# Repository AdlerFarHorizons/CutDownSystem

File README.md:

CutDownSystem
=============

Summary
-------
This is an arduino-based system for separating a high-altitude balloon from its payload under
pre-determined conditions.

Documentation
------------
The documentation available for this system is included in the /docs directory.

Software
--------
In order to run this system, two Arduino boards are required, assembled according to the SCHEMATIC
file. They are pre-programmed; to modify this system, a computer running Arduino IDE is required.
To program the Arduinos, upload new code as specified through the Arduino IDE to the CutDownBase.
The CutDownBase will wirelessly transfer pertinent code to the CutDownRemote.

Licensing
--------
Please see the file named LICENSE.

Contacts
--------

Lou Nigra
Adler Planetarium - Far Horizons Lab

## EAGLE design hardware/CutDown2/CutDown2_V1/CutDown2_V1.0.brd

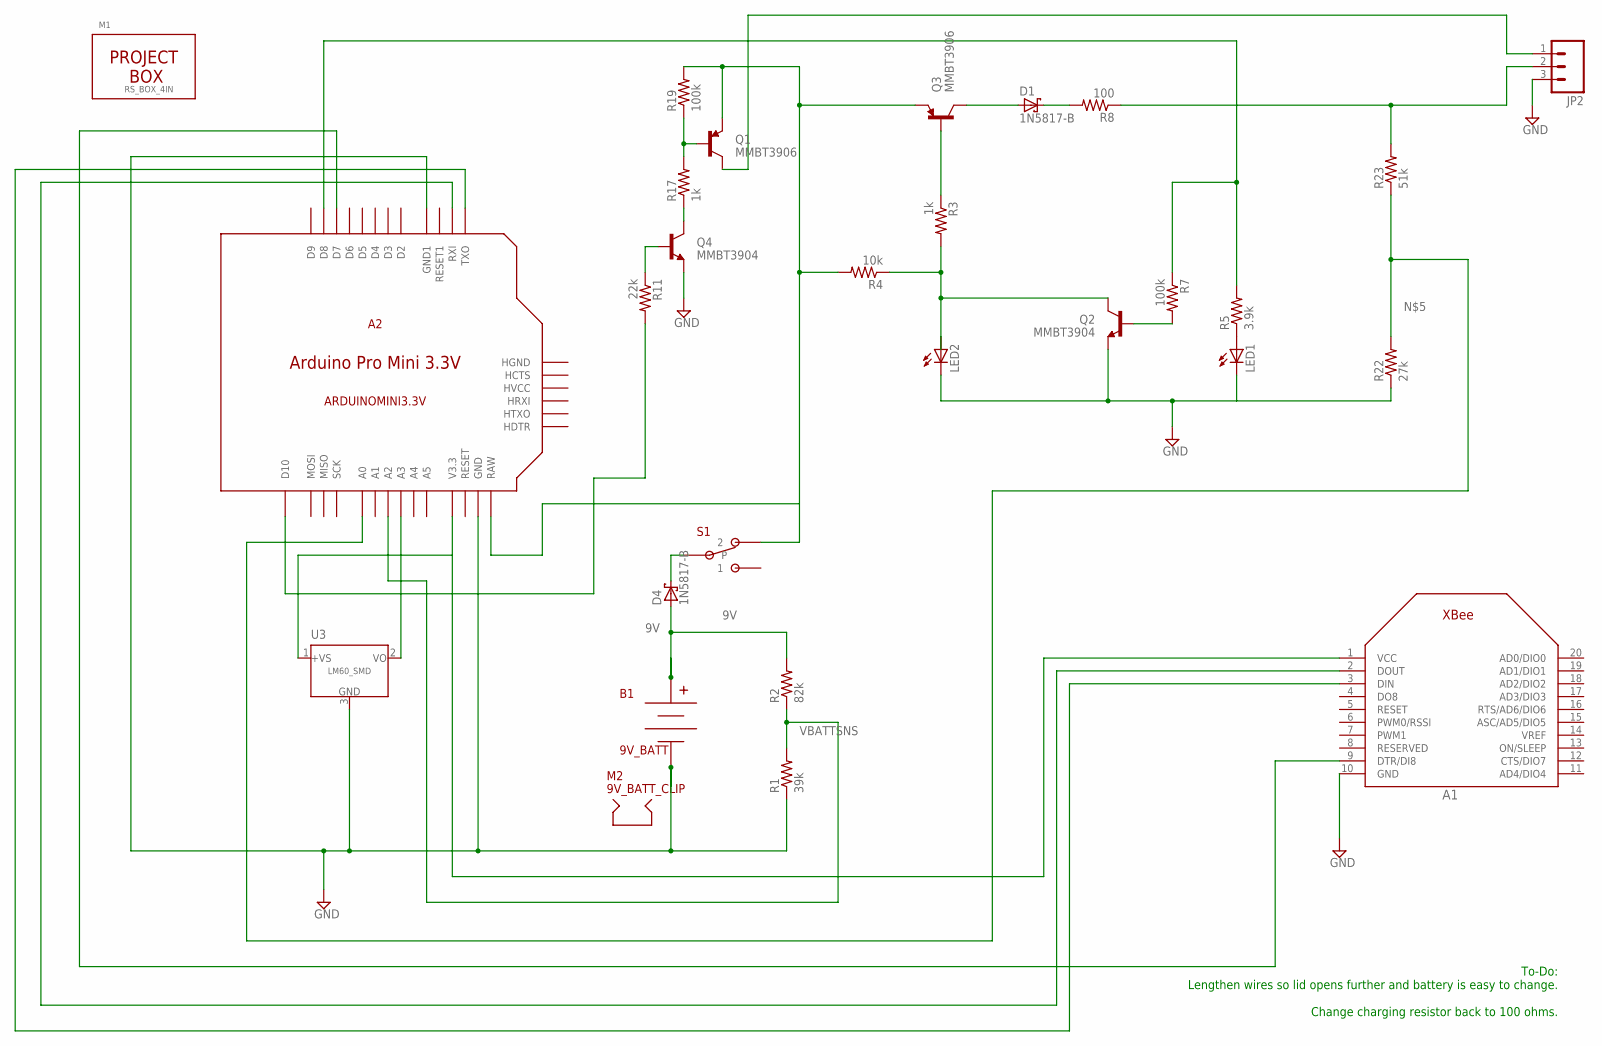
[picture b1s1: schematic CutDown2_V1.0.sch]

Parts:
A1: XBEE
A2: ARDUINOMINI3.3V
B1: 9V_BATT; KEYSTONE_593_594
D1, D4: 1N5817-B; DO41-7.6
JP2: M03POLAR_LOCK; MOLEX-1X3_LOCK
LED1, LED2: LED_ELD260; LED_LD260
M1: RS_BOX_4IN; RS_BOX_OUTLINE_4IN
M2: 9V_BATT_CLIP; KEYSTONE_9V_CLIP_H
Q1, Q3: MMBT3906; SOT23
Q2, Q4: MMBT3904; SOT23
R1: 39k; R0805
R2: 82k; R0805
R3, R17: 1k; R0805
R4: 10k; R0805
R5: 3.9k; R0805
R7, R19: 100k; R0805
R8: 100; R0805
R11: 22k; R0805
R22: 27k; R0805
R23: 51k; R0805
S1: APEM_SPDT_25000NH
U3: LM60_SMD; SOT23-3

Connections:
9V: B1.P$1 (V+), B1.P$2 (V+), B1.P$3 (V+), D4.A, R2.2
GND: A1.10 (GND), A2.P$9 (GND1), A2.P$20 (GND), B1.P$4 (V-), B1.P$5 (V-), B1.P$6 (V-), JP2.3, LED1.K (C), LED2.K (C), Q2.2 (E), Q4.2 (E), R1.1, R22.1, U3.3 (GND)
unnamed: Q3.1 (B), R3.1
unnamed: D1.A, Q3.3 (C)
unnamed: A2.P$2 (D8), R5.2, R7.1
unnamed: LED1.A, R5.1
unnamed: A2.P$26 (A0), R22.2, R23.1
unnamed: D1.C, R8.2
unnamed: LED2.A, Q2.3 (C), R3.2, R4.1
unnamed: A1.2 (DOUT), A2.P$11 (RXI)
unnamed: A2.P$23 (A3), U3.2 (VO)
unnamed: A1.3 (DIN), A2.P$12 (TXO)
unnamed: D4.C, S1.P$3
unnamed: Q2.1 (B), R7.2
unnamed: Q4.3 (C), R17.1
unnamed: Q1.1 (B), R17.2, R19.1
unnamed: JP2.1, Q1.3 (C)
unnamed: A2.P$30 (D10), R11.2
unnamed: Q4.1 (B), R11.1
unnamed: JP2.2, R8.1, R23.2
unnamed: A2.P$19 (RAW), Q1.2 (E), Q3.2 (E), R4.2, R19.2, S1.P$2 (2)
VBATTSNS: A2.P$24 (A2), R1.2, R2.1
VCC: A1.1 (VCC), A2.P$22 (V3.3), U3.1 (+VS)
VCSNS: A1.9 (DTR/DI8), A2.P$3 (D7)

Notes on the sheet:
To-Do: Lengthen wires so lid opens further and battery is easy to change. Change charging resistor back to 100 ohms.

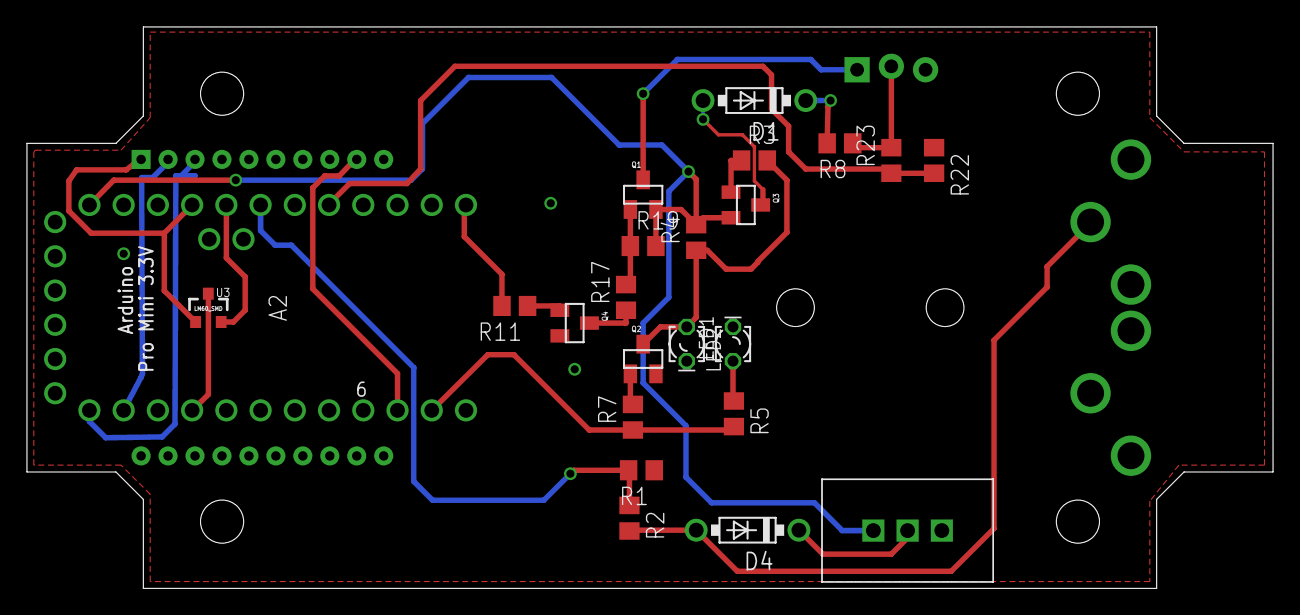
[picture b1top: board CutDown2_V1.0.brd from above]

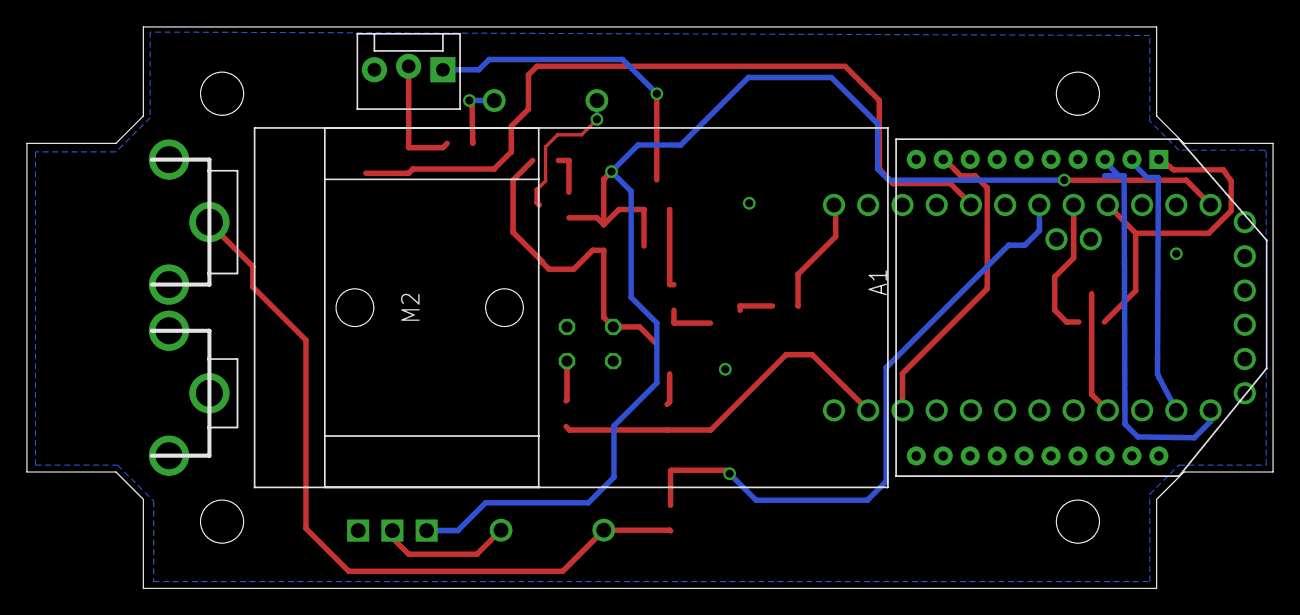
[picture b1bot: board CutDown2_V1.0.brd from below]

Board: 2 copper layers, 92.5 x 41.7 mm, 28 parts (4 on the bottom side), 24 nets.

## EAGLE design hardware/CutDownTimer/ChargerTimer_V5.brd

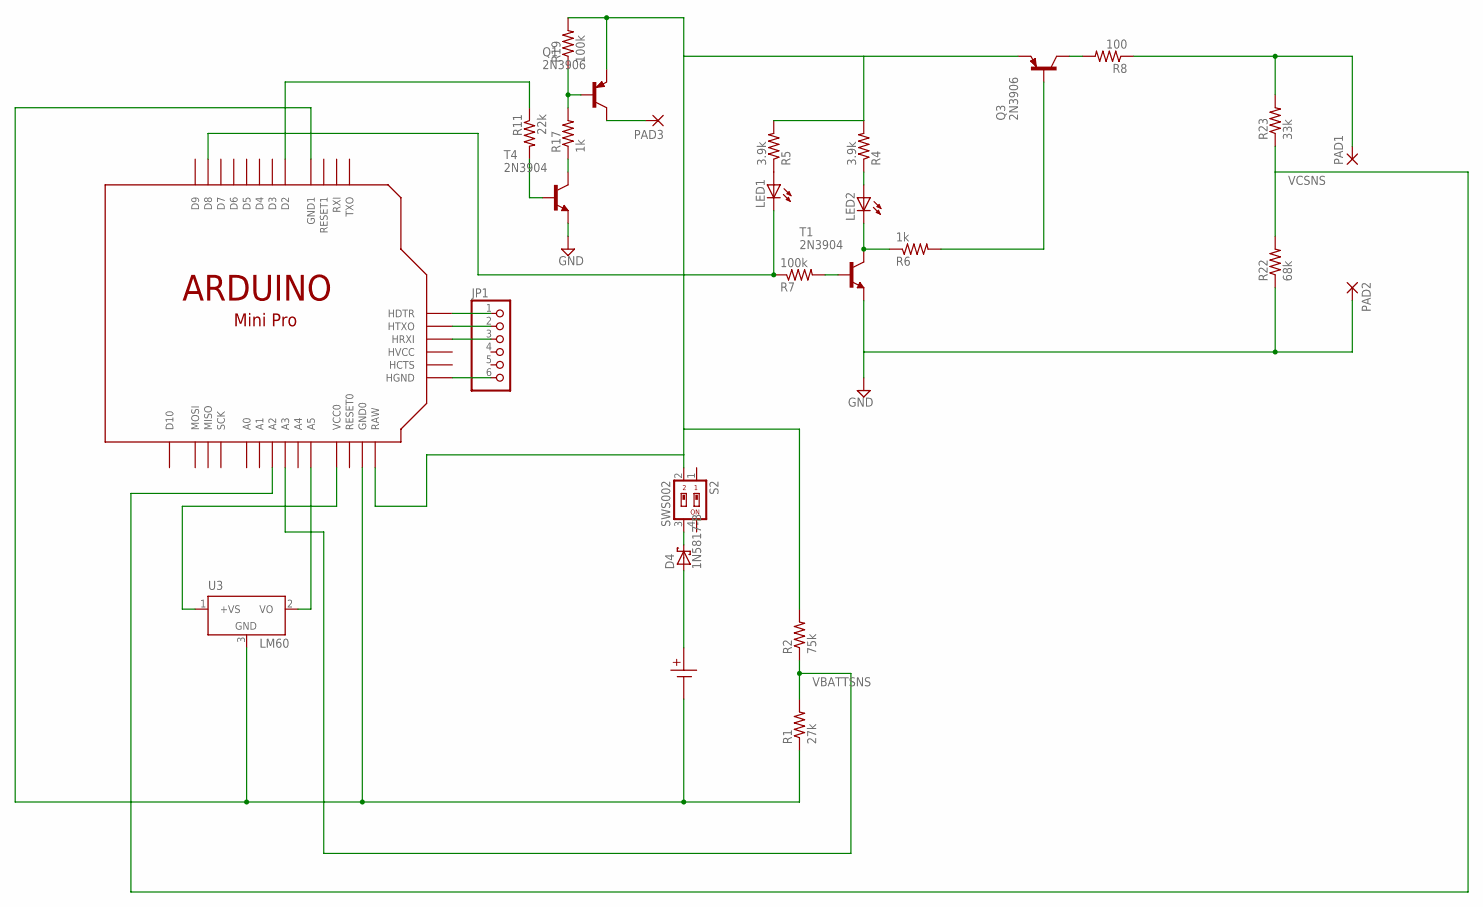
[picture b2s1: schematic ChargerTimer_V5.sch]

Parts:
D4: 1N5817-B; DO41-7.6
JP1: PINHD-1X6; 1X06
LED1, LED2: LED_ELD260; LED_LD260
PAD1, PAD2, PAD3: 2,15/1,0
Q1, Q3: 2N3906; TO92
R1: 27k; 0207/7
R2: 75k; 0207/7
R4, R5: 3.9k; 0207/7
R6, R17: 1k; 0207/7
R7, R19: 100k; 0207/7
R8: 100; 0207/7
R11: 22k; 0207/7
R22: 68k; 0207/7
R23: 33k; 0207/7
S2: SWS002; SMS-002
T1, T4: 2N3904; TO92
U3: LM60; TO92
U$1: BH1000G
U$4: ARDUINOMINI

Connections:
GND: T1.3 (E), T4.3 (E)
unnamed: Q3.1 (C), R8.2
unnamed: LED1.K (C), R7.1, U$4.P$2 (D8)
unnamed: LED1.A, R5.1
unnamed: LED2.A, R4.1
unnamed: LED2.K (C), R6.1, T1.1 (C)
unnamed: Q3.2 (B), R6.2
unnamed: D4.C, S2.3
unnamed: PAD2.1, R22.1
unnamed: R11.1, U$4.P$8 (D2)
unnamed: Q1.3 (E), Q3.3 (E), R2.2, R4.2, R5.2, R19.2, S2.2, U$4.P$19 (RAW)
unnamed: R7.2, T1.2 (B)
unnamed: R17.1, T4.1 (C)
unnamed: Q1.2 (B), R17.2, R19.1
unnamed: PAD3.1, Q1.1 (C)
unnamed: U3.2 (VO), U$4.P$35 (A5)
unnamed: JP1.1, U$4.P$13 (HDTR)
unnamed: U3.1 (+VS), U$4.P$22 (VCC0)
unnamed: R11.2, T4.2 (B)
unnamed: JP1.2, U$4.P$14 (HTXO)
unnamed: R1.1, U3.3 (GND), U$1.NEG$2 (P2), U$4.P$9 (GND1), U$4.P$20 (GND0)
unnamed: D4.A, U$1.POS$1 (P1)
unnamed: JP1.3, U$4.P$15 (HRXI)
unnamed: JP1.6, U$4.P$18 (HGND)
unnamed: PAD1.1, R8.1, R23.2
VBATTSNS: R1.2, R2.1, U$4.P$23 (A3)
VCSNS: R22.2, R23.1, U$4.P$24 (A2)

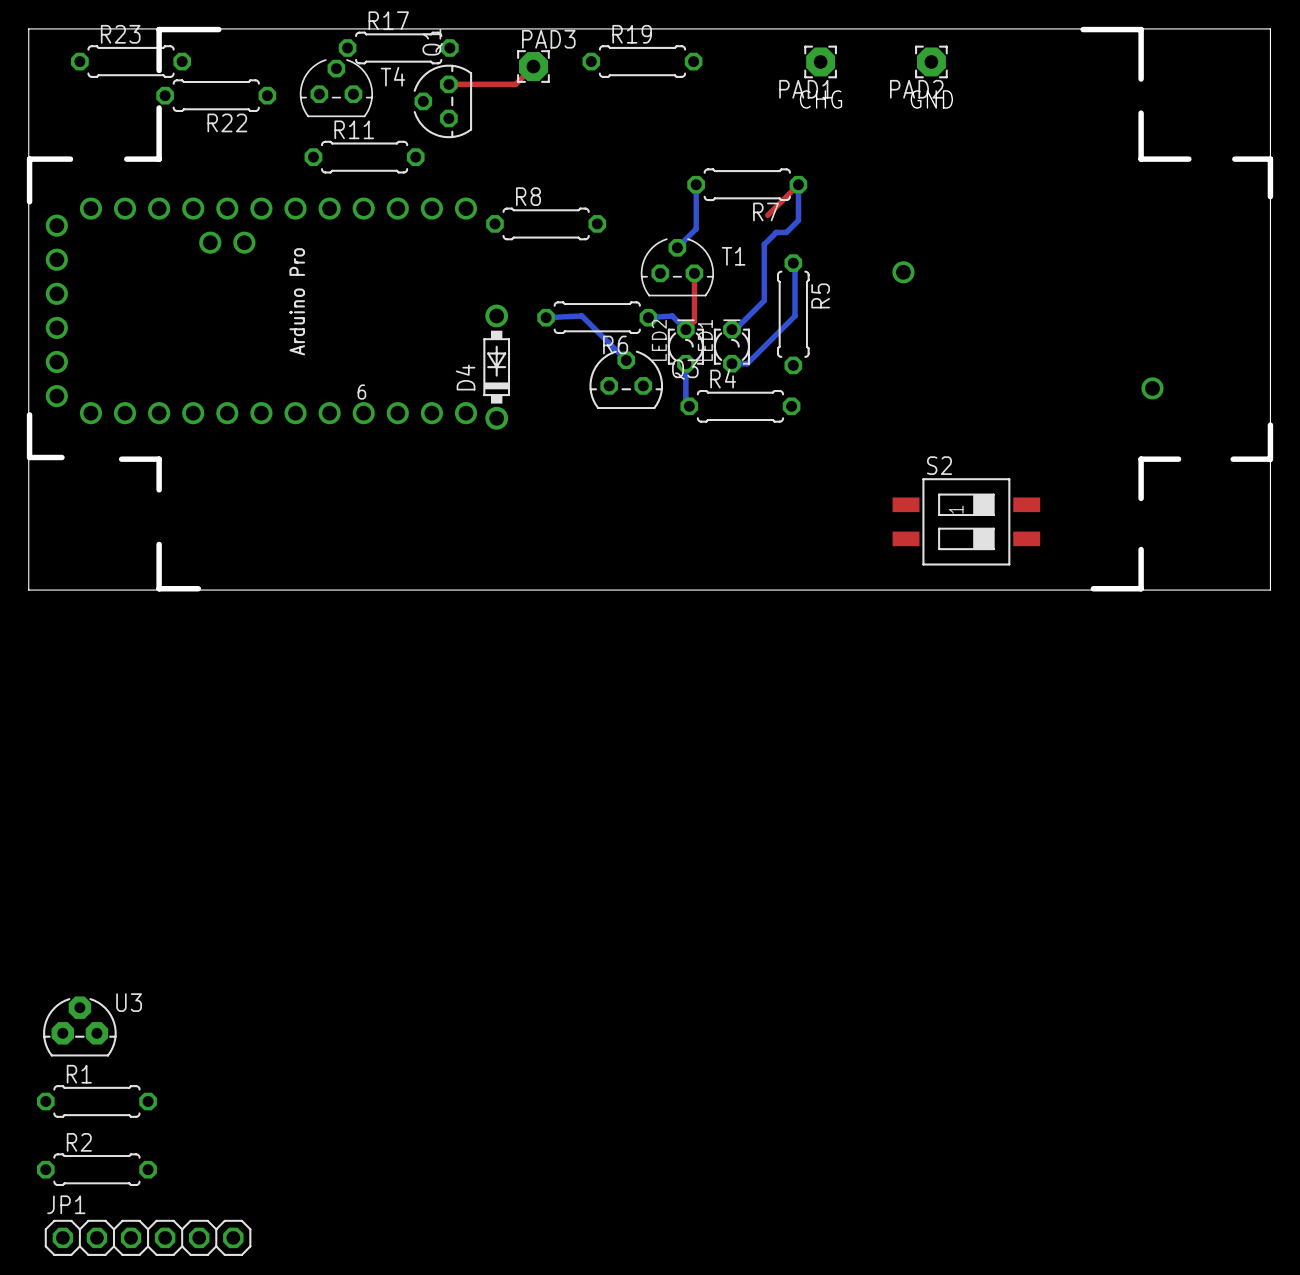
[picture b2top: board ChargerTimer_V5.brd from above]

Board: 2 copper layers, 92.5 x 41.8 mm, 27 parts (1 on the bottom side), 27 nets.

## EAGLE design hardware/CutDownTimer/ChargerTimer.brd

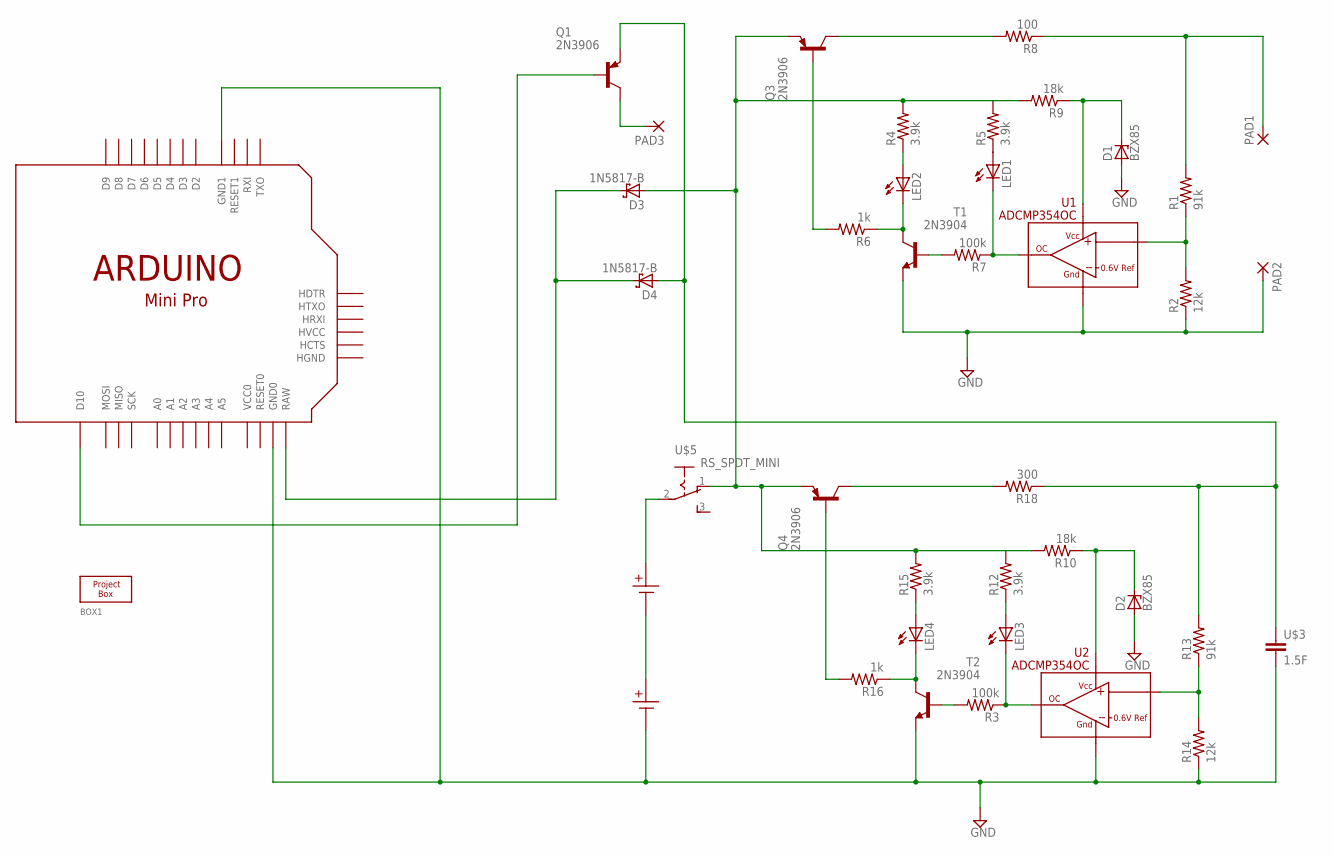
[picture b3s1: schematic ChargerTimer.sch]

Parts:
BOX1: RS_BOX_4IN; RS_BOX_OUTLINE_4IN
D1, D2: BZX85; DO41Z10
D3, D4: 1N5817-B; DO41-7.6
LED1, LED2, LED3, LED4: LED_ELD260; LED_LD260
PAD1, PAD2, PAD3: 2,15/1,0
Q1, Q3, Q4: 2N3906; TO92
R1, R13: 91k; 0207/7
R2, R14: 12k; 0207/7
R3, R7: 100k; 0207/7
R4, R5, R12, R15: 3.9k; 0207/7
R6, R16: 1k; 0207/7
R8: 100; 0207/7
R9, R10: 18k; 0207/7
R18: 300; 0207/7
T1, T2: 2N3904; TO92
U1, U2: ADCMP354OC; ADCMP35X
U$1, U$2: BH1000G
U$3: 1.5F; SUPERCAP1.0/0.85H
U$4: ARDUINOMINI
U$5: RS_SPDT_MINI

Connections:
GND: D1.A, D2.A, PAD2.1, R2.1, R14.1, T1.3 (E), T2.3 (E), U1.P2 (GND), U2.P2 (GND), U$2.NEG$2 (P2), U$3.P$2 (2), U$4.P$9 (GND1), U$4.P$20 (GND0)
unnamed: R1.1, R2.2, U1.P1 (IN)
unnamed: Q3.1 (C), R8.2
unnamed: LED1.K (C), R7.1, U1.P3 (OUT)
unnamed: LED1.A, R5.1
unnamed: LED2.A, R4.1
unnamed: LED2.K (C), R6.1, T1.1 (C)
unnamed: Q3.2 (B), R6.2
unnamed: PAD1.1, R1.2, R8.1
unnamed: R3.2, T2.2 (B)
unnamed: D4.A, Q1.3 (E), R13.2, R18.1, U$3.P$1 (1)
unnamed: U$1.POS$1 (P1), U$5.2
unnamed: U$1.NEG$2 (P2), U$2.POS$1 (P1)
unnamed: R7.2, T1.2 (B)
unnamed: D1.C, R9.1, U1.P4 (VCC)
unnamed: D2.C, R10.1, U2.P4 (VCC)
unnamed: R13.1, R14.2, U2.P1 (IN)
unnamed: LED3.K (C), R3.1, U2.P3 (OUT)
unnamed: LED3.A, R12.1
unnamed: LED4.A, R15.1
unnamed: LED4.K (C), R16.1, T2.1 (C)
unnamed: Q4.2 (B), R16.2
unnamed: Q4.1 (C), R18.2
unnamed: D3.A, Q3.3 (E), Q4.3 (E), R4.2, R5.2, R9.2, R10.2, R12.2, R15.2, U$5.1 (O)
unnamed: PAD3.1, Q1.1 (C)
unnamed: D3.C, D4.C, U$4.P$19 (RAW)
unnamed: Q1.2 (B), U$4.P$30 (D10)

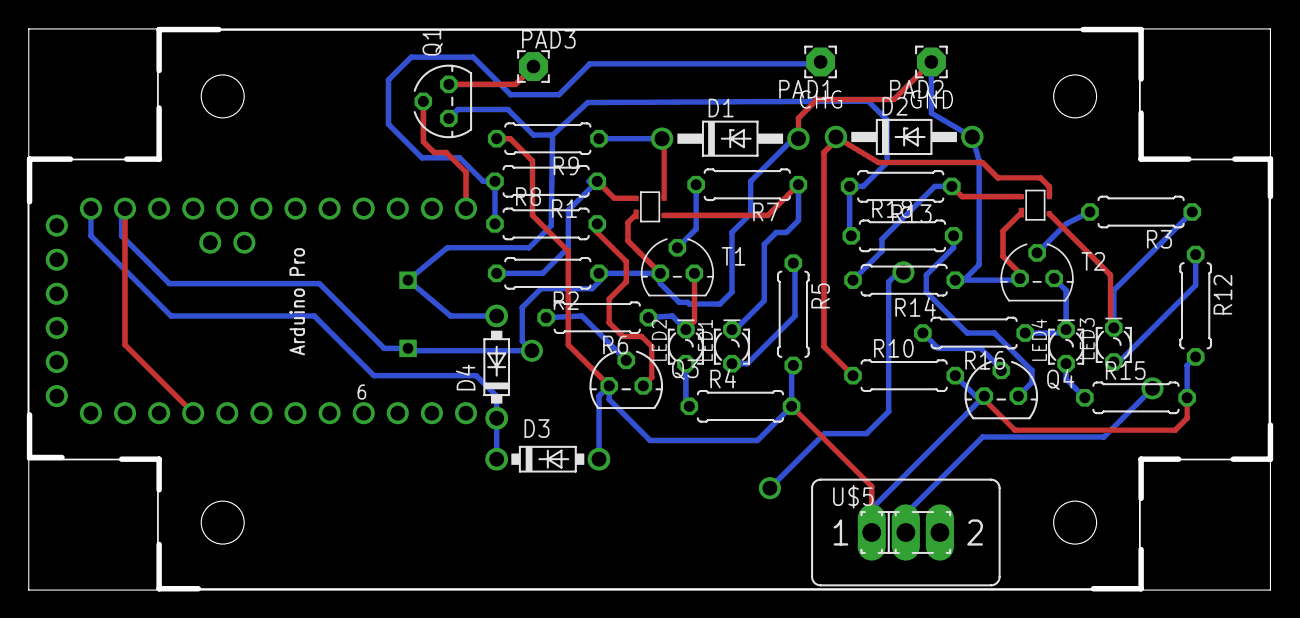
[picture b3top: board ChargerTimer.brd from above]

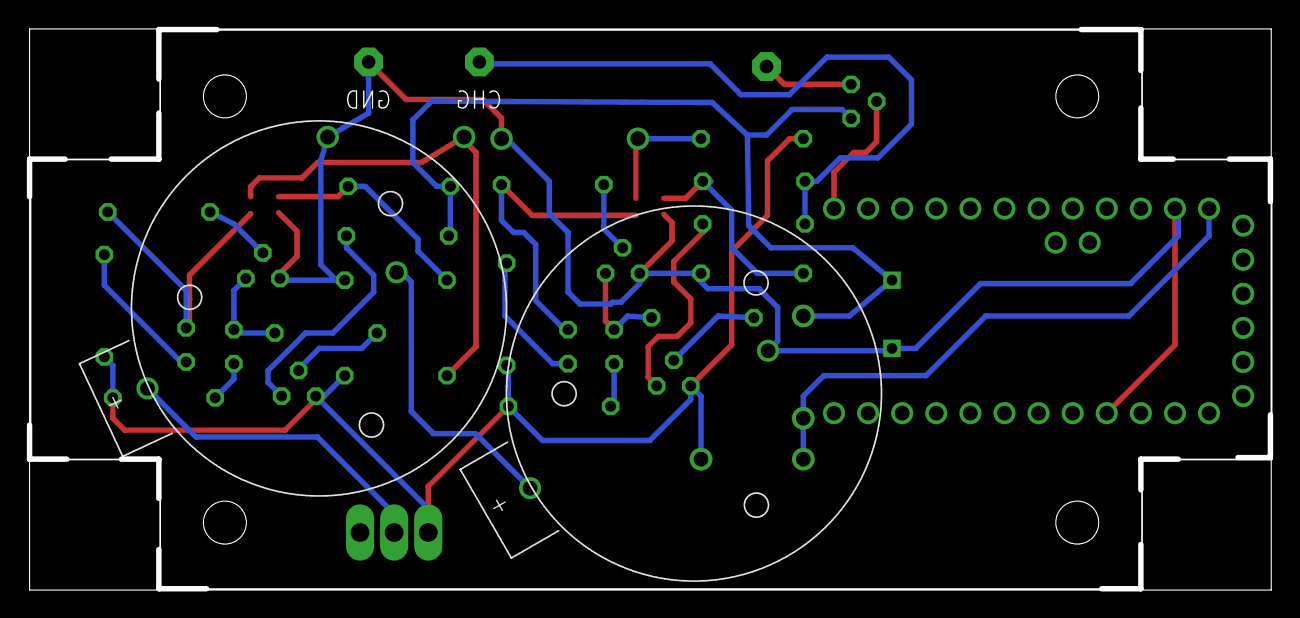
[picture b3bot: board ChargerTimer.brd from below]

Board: 2 copper layers, 92.5 x 41.8 mm, 40 parts (3 on the bottom side), 27 nets.

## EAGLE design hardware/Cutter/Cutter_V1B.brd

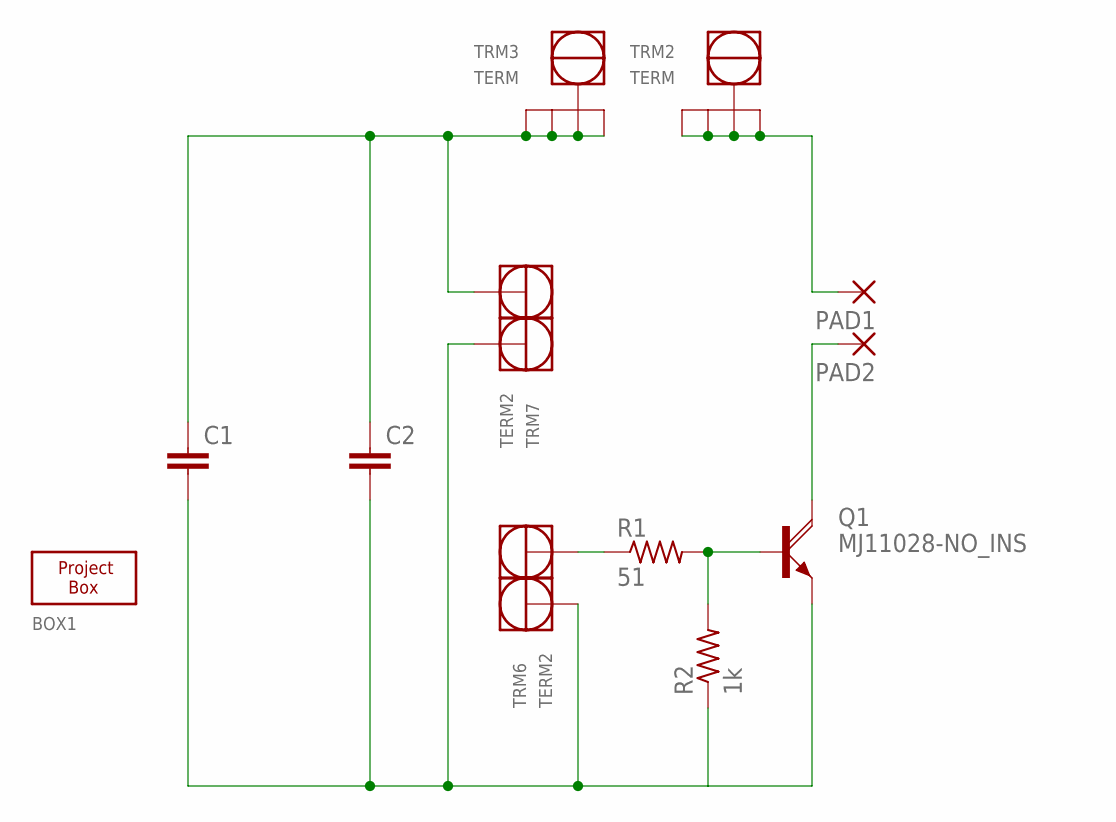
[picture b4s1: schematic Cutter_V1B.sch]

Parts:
BOX1: RS_BOX_3IN; RS_BOX_OUTLINE_3IN
C1, C2: C1400X850; SUPERCAP1.4/0.85H
PAD1, PAD2: 2,15/1,0
Q1: MJ11028-NO_INS; TO-3-NO_INSULATOR
R1: 51; 0207/10
R2: 1k; 0207/10
TRM2, TRM3: TERM; SCREWTERM-300MILSQ
TRM6, TRM7: TERM2; SCREWTERMBLK-DUAL

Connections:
C: PAD2.1, Q1.C, Q1.C1 (C)
unnamed: C1.P$2 (2), C2.P$2 (2), Q1.E, R2.1, TRM6.P$1 (P1), TRM7.P$1 (P1)
unnamed: C1.P$1 (1), C2.P$1 (1), TRM3.P$1 (P1), TRM3.P$2 (P2), TRM3.P$3 (P3), TRM3.P$4 (P4), TRM7.P$2 (P2)
unnamed: PAD1.1, TRM2.P$1 (P1), TRM2.P$2 (P2), TRM2.P$3 (P3), TRM2.P$4 (P4)
unnamed: Q1.B, R1.2, R2.2
unnamed: R1.1, TRM6.P$2 (P2)

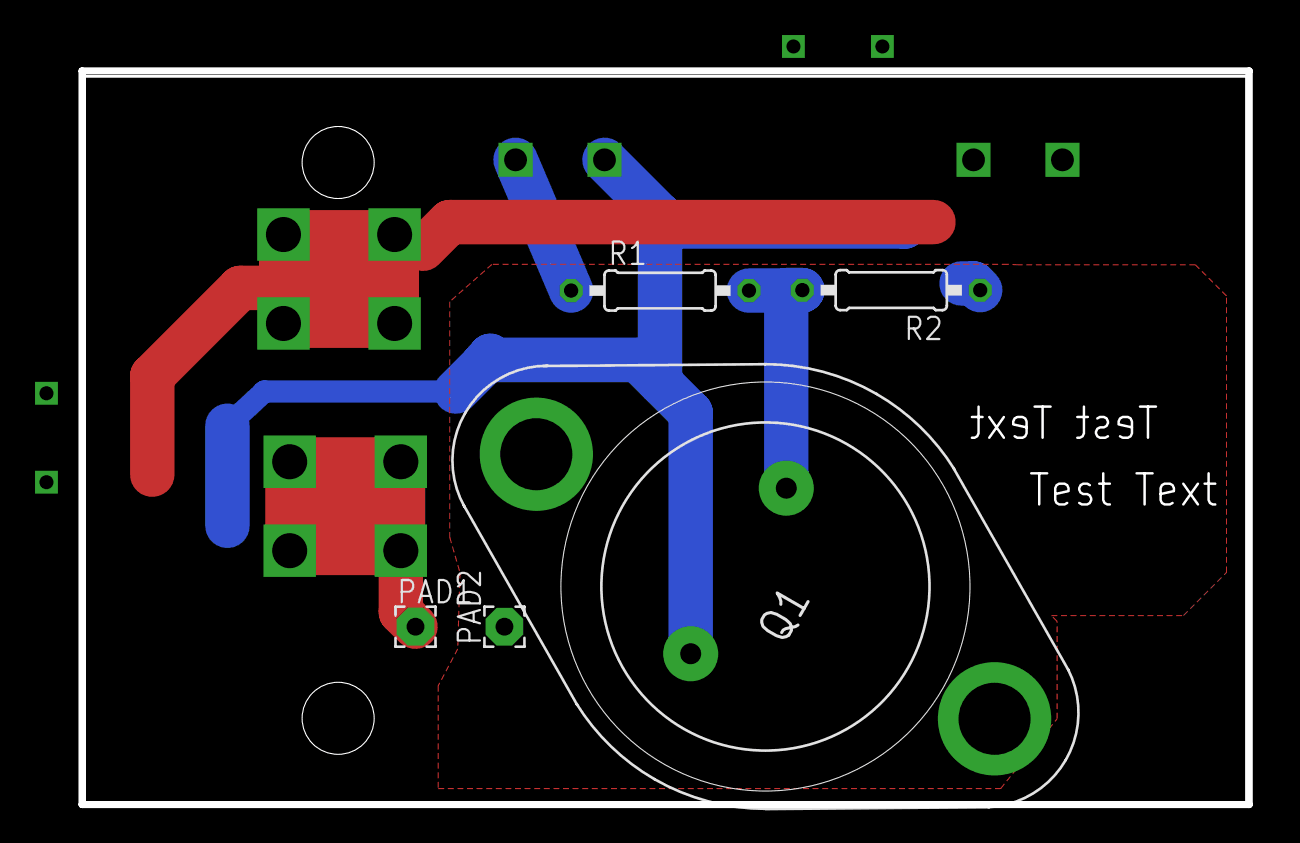
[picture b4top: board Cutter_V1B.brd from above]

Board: 2 copper layers, 66.7 x 41.9 mm, 12 parts (0 on the bottom side), 6 nets.

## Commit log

2014-07-12 Initial commit.
2014-07-12 Added CutDownBase and CutDownRemote Code from Drive
2014-07-12 Removed Documentation, Changed Narcoleptic to MsTimer2
2014-07-12 Added Documentation (previously located in code) to doc folder
    Documentation is formatted as a LibreOffice file.
2014-07-18 Moved all documentation to ReadMe files
2014-07-19 Remote: Added Start/Stop Switch, Set Switch, Vars Switch, Timer LED, Set LED, and Vars LEDs; UP/DOWN Switches not yet implemented; Not enough pins for all elements
2014-07-19 Started display code
2014-07-19 Remote: Added all LEDs and Switches, Removed large portions of old code. Documentation: Edited and updated main README and CutDownRemote documentation
2014-08-09 Kelli 6/30 changes
2014-08-10 Kelli's 8/10/2014 changes
2014-08-24 Initial schematic
2014-08-24 Kelli's 23-Aug-2104 changes
2014-08-24 Add wiki files locally as submodule
2014-08-30 Kelli+Rachel upcounter display proto
2014-08-30 Kelli's status update
2014-08-31 Rachael: Added initial skeleton of Hysteresis for capacitor charging; cleaned up variables; removed standby variable in favor of using active to tell whether Remote is in standby.
2014-11-09 Latest changes
2015-03-28 Latest wiki
2015-04-17 New CutDown prototype initially for tethered parasail drop tests
2015-04-17 Fixed green light function
    Green light now turns off on base when disconnected from remote.

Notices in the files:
parts and their libraries:
SparkFun-Connectors: Licensing: Creative Commons ShareAlike 4.0 International - https://creativecommons.org/licenses/by-sa/4.0
